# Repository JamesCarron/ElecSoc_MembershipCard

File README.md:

# ElecSoc Soldering Practice Card - JayceDesign - August 2024

## Introduction
The practice card is an oscillating circuit with a 555 timer. It blinks 2 sets of LEDs. The oscillating period is controlled with an RC circuit.

## Assembling the board
The board has 2 sets of components. Required and optional components. The required components are the minimum components needed to assemble to have a working card. The optional components are for soldering practice and to change the oscillator circuit. The required components are marked with an asterisk in the board.
To assemble the card, start with the bigger packages first. There are 4 different packages: 1206, 0805, 0603 and 0402. The bigger the number, the bigger the component, and easier to solder it will be. Start with the practice components first. Assemble first the optional 1206 resistors, then the 0805 LEDs. Then, move on to the practice network on the bottom left of the card. Then, start placing on the required components, from the largest package to the smallest. Lastly, solder on the 555 timer and the pin headers on the left.

_The order of soldering is indicated above._

In red, the practice components. Green, components to assemble once comfortable with the process. Orange, extra components for tuning oscillating circuit. You don't need to solder all optional components, only as many as you need to feel comfortable with the soldering process.
## Testing
If properly assembled, when the card is powered, the LEDs will blink with a period of 1.5s. The practice network is a voltage divider. The voltage drop at the lower resistors should be 1.25V.
If you add the 5Ω resistor on the top right, you can slot the card in a USB port.
You can add the optional resistors for the oscillator circuit. This will reduce the period to about 0.8s. Adding only the extra capacitor will increase the period to 3.3s.

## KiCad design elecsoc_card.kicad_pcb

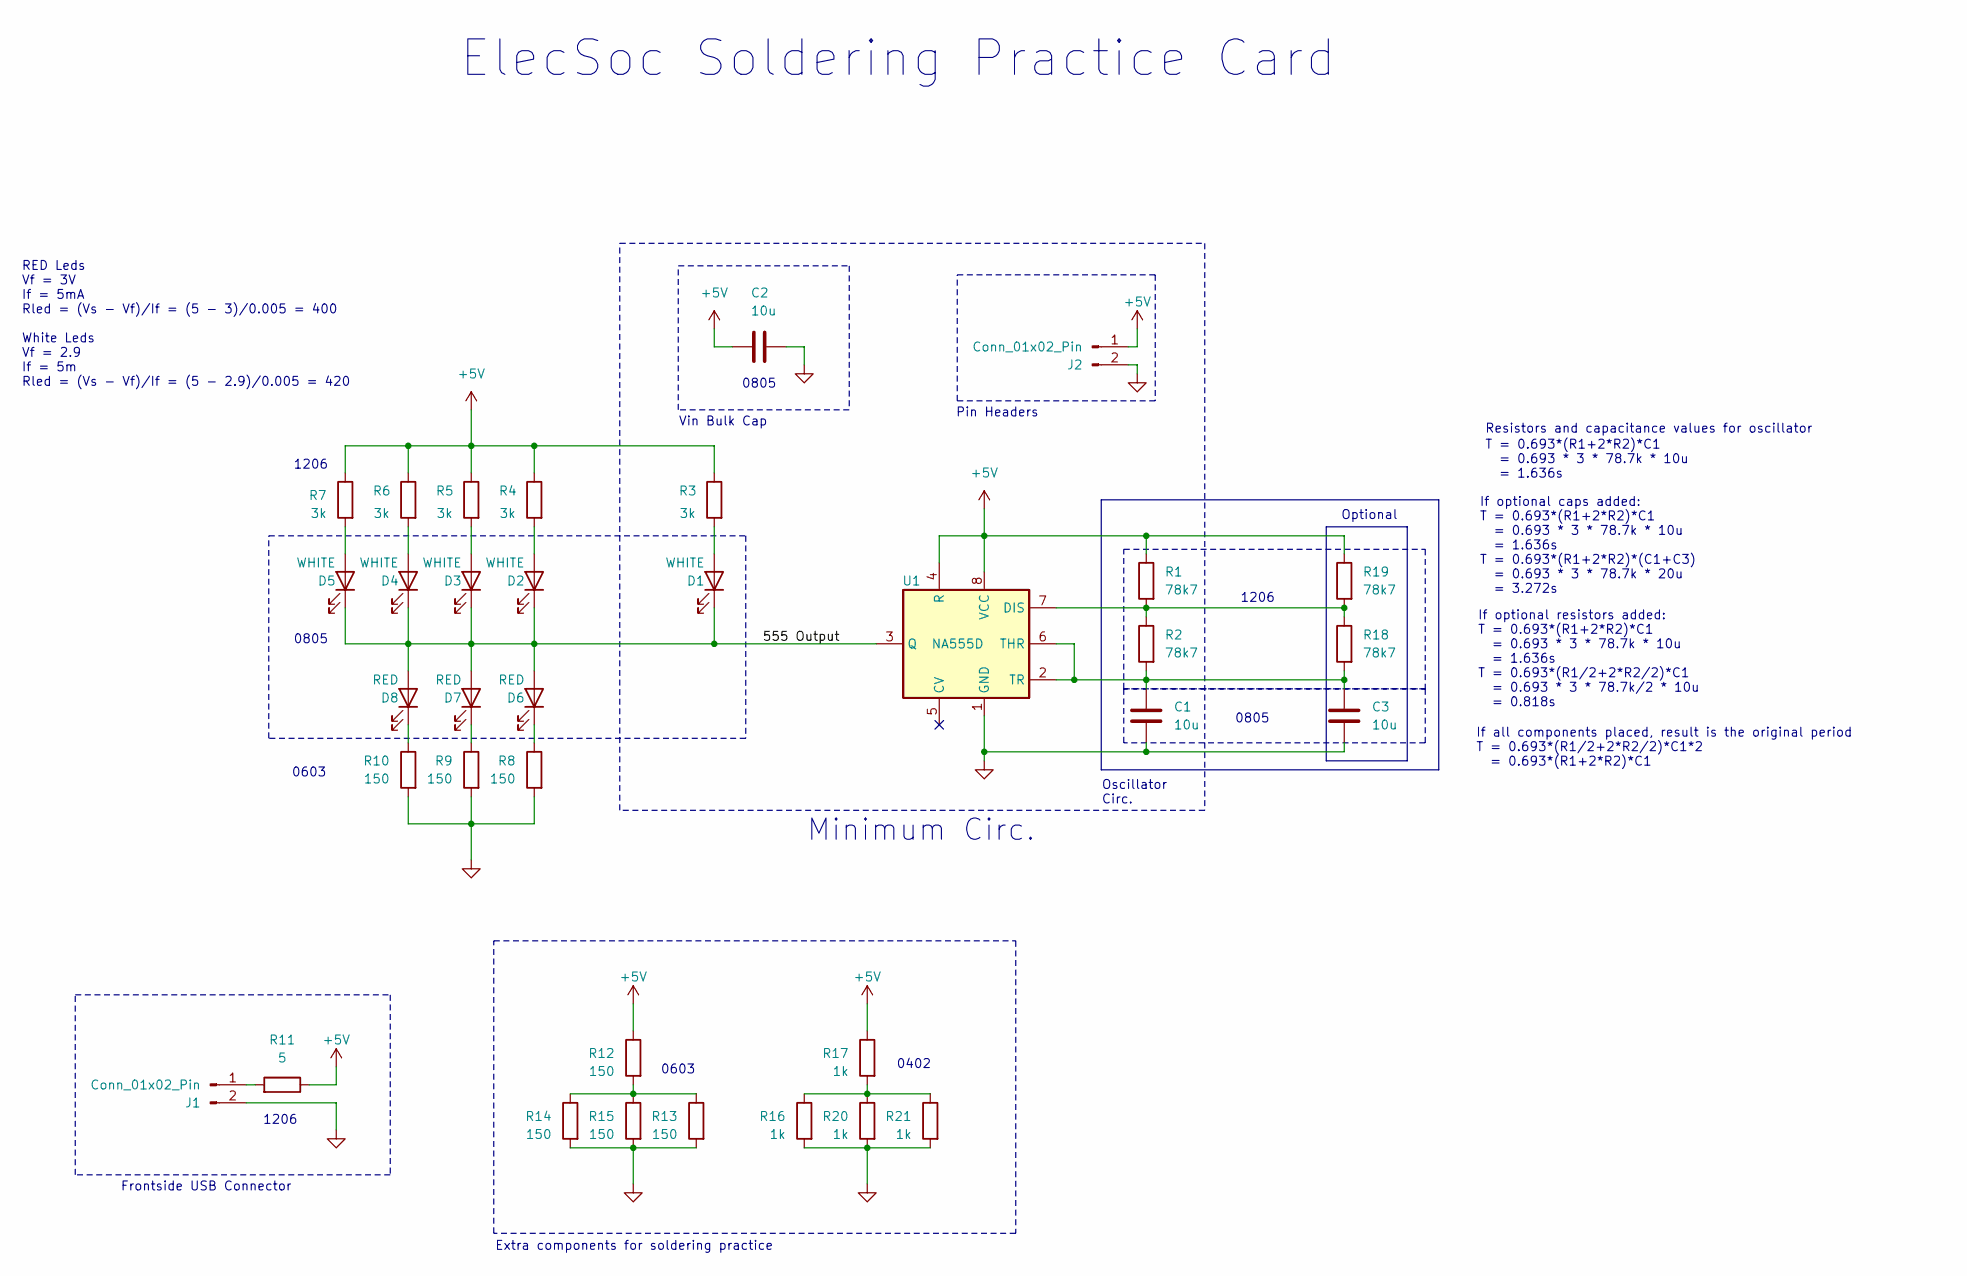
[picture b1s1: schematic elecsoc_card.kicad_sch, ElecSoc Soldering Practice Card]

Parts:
C1, C2, C3: 10u; C_0805_2012Metric_Pad1.18x1.45mm_HandSolder; MPN CL21A106KPFNNNF
D1, D2, D3, D4, D5: WHITE; LED_0805_2012Metric_Pad1.15x1.40mm_HandSolder; MPN SMLMN2WB1CW1
D6, D7, D8: RED; LED_0805_2012Metric_Pad1.15x1.40mm_HandSolder; MPN IN-S85AT5UW
J1: Conn_01x02_Pin; USB_A_Male_inboard
J2: Conn_01x02_Pin; PinHeader_2x01_P2.54mm_Vertical; MPN 826632-1
R1, R2, R18, R19: 78k7; R_1206_3216Metric; MPN RT1206FRE0778K7L
R3, R4, R5, R6, R7: 3k; R_1206_3216Metric; MPN RT1206FRE073KL
R8, R9, R10, R12, R13, R14, R15: 150; R_0603_1608Metric; MPN MCT06030C1500FP500
R11: 5; R_1206_3216Metric; MPN RT1206FRD075R1L
R16, R17, R20, R21: 1k; R_0402_1005Metric; MPN MCS04020C1001FE000
U1: NA555D; SOIC-8_3.9x4.9mm_P1.27mm; MPN 621-NE555S-13

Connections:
+5V: C2.1, J2.1, R1.1, R3.1, R4.1, R5.1, R6.1, R7.1, R11.1, R12.1, R17.1, R19.1, U1.4 (R), U1.8 (VCC)
/555 Output: D1.1 (K), D2.1 (K), D3.1 (K), D4.1 (K), D5.1 (K), D6.2 (A), D7.2 (A), D8.2 (A), U1.3 (Q)
GND: C1.2, C2.2, C3.2, J1.2, J2.2, R8.2, R9.2, R10.2, R13.2, R14.2, R15.2, R16.2, R20.2, R21.2, U1.1 (GND)
unnamed: D5.2 (A), R7.2
unnamed: D4.2 (A), R6.2
unnamed: D3.2 (A), R5.2
unnamed: D1.2 (A), R3.2
unnamed: D2.2 (A), R4.2
unnamed: D6.1 (K), R8.1
unnamed: D7.1 (K), R9.1
unnamed: D8.1 (K), R10.1
unnamed: J1.1, R11.2
unnamed: R12.2, R13.1, R14.1, R15.1
unnamed: R16.1, R17.2, R20.1, R21.1
unnamed: R1.2, R2.1, R18.1, R19.2, U1.7 (DIS)
unnamed: C1.1, C3.1, R2.2, R18.2, U1.2 (TR), U1.6 (THR)

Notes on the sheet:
Frontside USB Connector
Minimum Circ.
1206
RED Leds Vf = 3V If = 5mA Rled = (Vs - Vf)/If = (5 - 3)/0.005 = 400 White Leds Vf = 2.9 If = 5m Rled = (Vs - Vf)/If = (5 - 2.9)/0.005 = 420
If optional resistors added: T = 0.693*(R1+2*R2)*C1 = 0.693 * 3 * 78.7k * 10u = 1.636s T = 0.693*(R1/2+2*R2/2)*C1 = 0.693 * 3 * 78.7k/2 * 10u = 0.818s
0603
If optional caps added: T = 0.693*(R1+2*R2)*C1 = 0.693 * 3 * 78.7k * 10u = 1.636s T = 0.693*(R1+2*R2)*(C1+C3) = 0.693 * 3 * 78.7k * 20u = 3.272s
Pin Headers
0805
0402
Vin Bulk Cap
Oscillator Circ.
Resistors and capacitance values for oscillator
If all components placed, result is the original period T = 0.693*(R1/2+2*R2/2)*C1*2 = 0.693*(R1+2*R2)*C1
Optional
ElecSoc Soldering Practice Card
T = 0.693*(R1+2*R2)*C1 = 0.693 * 3 * 78.7k * 10u = 1.636s
Extra components for soldering practice

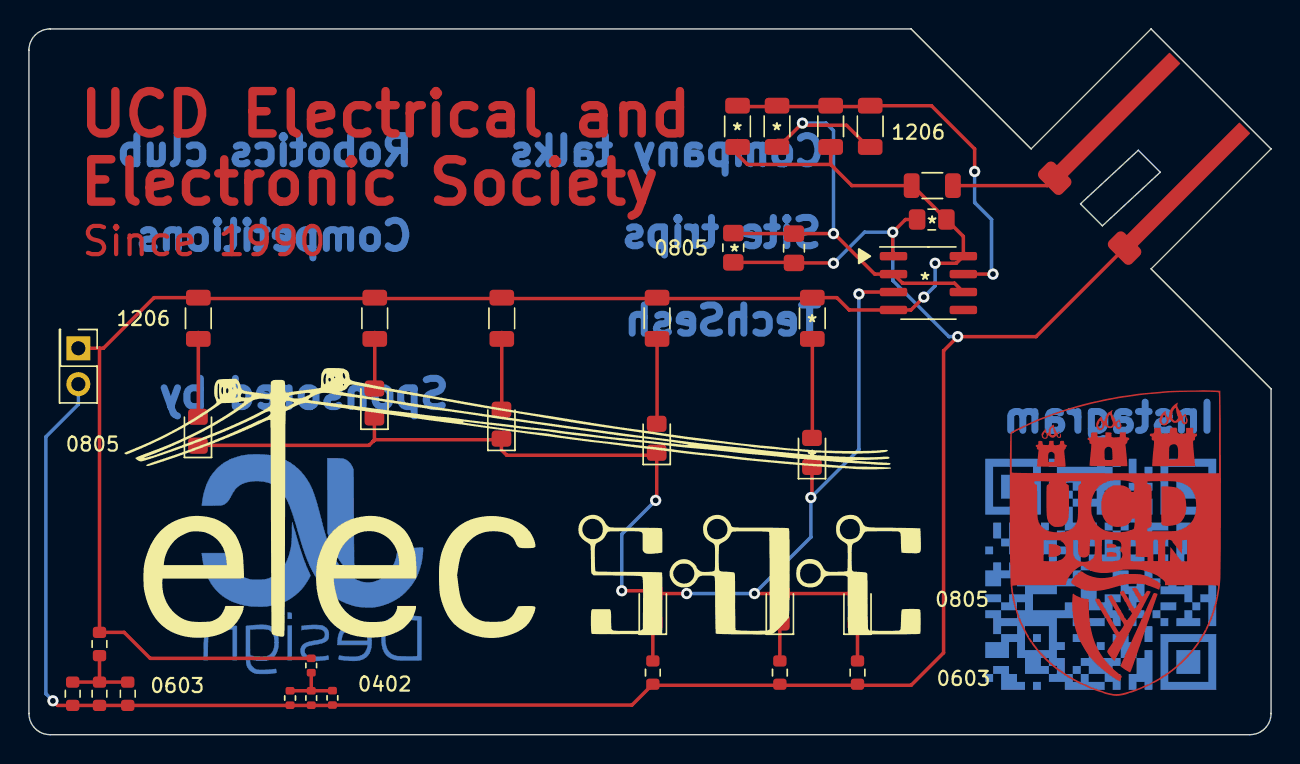
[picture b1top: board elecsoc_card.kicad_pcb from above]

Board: 2 copper layers, 88.0 x 50.0 mm, 35 parts (0 on the bottom side), 16 nets.

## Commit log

2023-08-22 Added Manufacturing Images
2023-08-23 Changed R3-R7 to 390
2023-08-23 Added Mouser Part Order 230823
2023-08-23 SchematicCleanup
2023-09-06 Generated IBOM File
2023-09-06 Removed Items for Rev2, for Daniel to complete
2023-09-06 Routing added
2023-09-06 Added silkscreen on usb port
2023-09-06 Protection resistor and capacitor + cut for 3d printed part
2023-09-06 Caps added and resistors changed
2023-09-06 Changed resistors
2023-09-06 Manufacturer files
2023-09-06 No files in manufacturer folder
2023-09-06 Rev2 Design Freeze
2023-09-06 As Ordered on JLCPCB - OrderRef: W202309070430314
2023-09-20 Updated PCB values from schematic, created interactive BOM, deleted unnecessary backups
2024-08-10 Added extra resistors for soldering practice
2024-08-10 Added extra parallel cap to see how the change in capacitance affects the period
2024-08-10 Added parallel resistors to change RC constant
2024-08-10 Values corrected
2024-08-10 Back to 80k
2024-08-10 New PCB design
2024-08-10 Updated PCB
2024-08-13 updated footprints, consolidated bom
2024-08-13 Package sizes updated
2024-08-13 Components placed and routed
2024-08-13 Silkscreen added
2024-08-13 PCB finished plus gerbers
2024-08-13 Gerbers generated
2024-08-13 BOM generated
2024-08-13 Interactive BOM created
2024-08-14 Added soldering instructions
2024-08-14 PDFs of designs created
2024-08-14 Fixed typos
2024-08-30 Updated, cant remember
